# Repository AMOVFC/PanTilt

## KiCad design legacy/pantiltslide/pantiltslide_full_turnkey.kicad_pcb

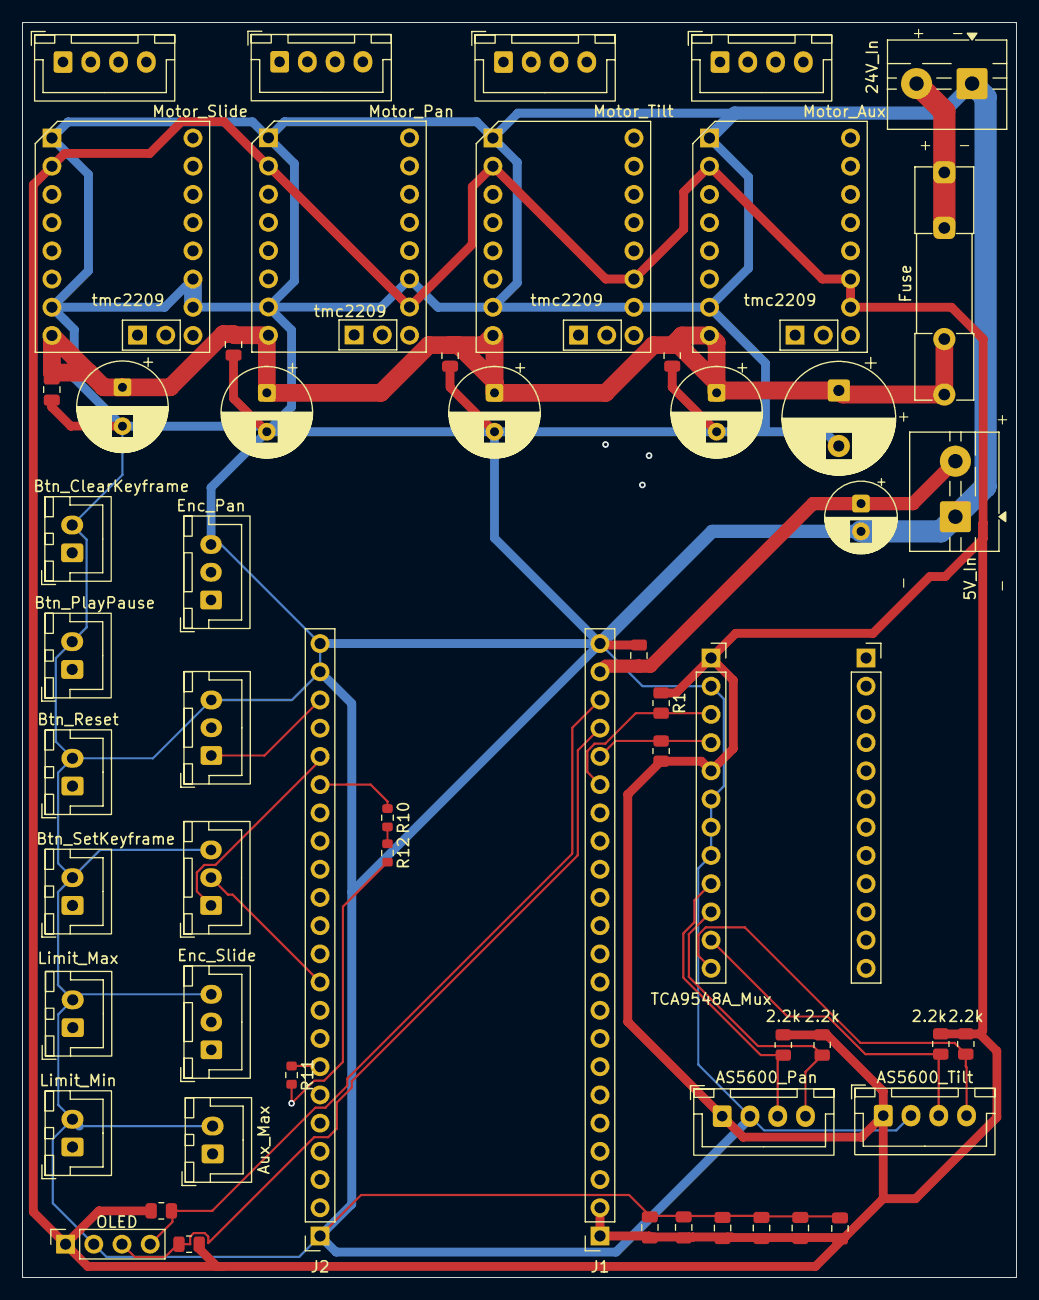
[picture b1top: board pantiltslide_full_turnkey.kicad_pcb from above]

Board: 4 copper layers, 89.5 x 113.0 mm, 57 parts (0 on the bottom side), 57 nets.

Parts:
C1: 470uF/50V; CP_Radial_D10.0mm_P5.00mm
C2, C3, C4, C5: 100uF/50V; CP_Radial_D8.0mm_P3.50mm
C6, C7, C8, C9: 100nF/50V; C_0805_2012Metric
C10: 100uF/16V; CP_Radial_D6.3mm_P2.50mm
C11, C13, C14, C15, C16, C17: 100nF; C_0805_2012Metric
C12: 22uF; C_0805_2012Metric
F1: Fuse; Fuseholder_Clip-5x20mm_Littelfuse_111_Inline_P20.00x5.00mm_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
J1, J2: Conn_01x22_Socket; PinSocket_1x22_P2.54mm_Vertical
J17: Motor_Slide; JST_XH_B4B-XH-A_1x04_P2.50mm_Vertical
J18: Motor_Pan; JST_XH_B4B-XH-A_1x04_P2.50mm_Vertical
J19: Motor_Tilt; JST_XH_B4B-XH-A_1x04_P2.50mm_Vertical
J20, J24: TCA9548A_Mux; PinSocket_1x12_P2.54mm_Vertical
J21: AS5600_Pan; JST_XH_B4B-XH-A_1x04_P2.50mm_Vertical
J22: AS5600_Tilt; JST_XH_B4B-XH-A_1x04_P2.50mm_Vertical
J23: OLED; PinSocket_1x04_P2.54mm_Vertical
J26: Limit_Min; JST_XH_B2B-XH-A_1x02_P2.50mm_Vertical
J27: Limit_Max; JST_XH_B2B-XH-A_1x02_P2.50mm_Vertical
J28: Motor_Aux; JST_XH_B4B-XH-A_1x04_P2.50mm_Vertical
J29: Enc_Slide; JST_XH_B3B-XH-A_1x03_P2.50mm_Vertical
J30: Enc_Pan; JST_XH_B3B-XH-A_1x03_P2.50mm_Vertical
J31: Enc_Tilt; JST_XH_B3B-XH-A_1x03_P2.50mm_Vertical
J32: Enc_Aux; JST_XH_B3B-XH-A_1x03_P2.50mm_Vertical
J33: Btn_SetKeyframe; JST_XH_B2B-XH-A_1x02_P2.50mm_Vertical
J34: Btn_ClearKeyframe; JST_XH_B2B-XH-A_1x02_P2.50mm_Vertical
J35: Btn_PlayPause; JST_XH_B2B-XH-A_1x02_P2.50mm_Vertical
J36: Btn_Reset; JST_XH_B2B-XH-A_1x02_P2.50mm_Vertical
J37: 5V_In; TerminalBlock_MaiXu_MX126-5.0-02P_1x02_P5.00mm
J38: 24V_In; TerminalBlock_MaiXu_MX126-5.0-02P_1x02_P5.00mm
J41: Aux_Max; JST_XH_B2B-XH-A_1x02_P2.50mm_Vertical
R1, R2, R3, R4: 4.7k; R_0805_2012Metric
R5, R6, R7, R8: 2.2k; R_0805_2012Metric
R10, R11: 100R; R_0603_1608Metric
R12: 1k R; R_0603_1608Metric
U1, U2, U3, U4: tmc2209; TMC2209_SilentStepStick_Socket_18P

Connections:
3.3v: C12.1, C13.1, C14.1, C15.1, C16.1, C17.1, J1.1, J1.2, J20.1, J20.5, J21.1, J22.1, J23.1, R1.1, R2.1, R3.1, R4.1, R5.1, R6.1, R7.1, R8.1, U1.2 (VIO), U2.2 (VIO), U2.15 (MS1), U3.2 (VIO), U3.14 (MS2), U4.2 (VIO), U4.14 (MS2), U4.15 (MS1)
+24V: C1.1, C2.1, C3.1, C4.1, C5.1, C6.1, C7.1, C8.1, C9.1, F1.2, U1.8 (VM), U2.8 (VM), U3.8 (VM), U4.8 (VM)
AUX_M1A: J28.1, U4.4 (M1A)
AUX_M1B: J28.2, U4.3 (M1B)
AUX_M2A: J28.3, U4.5 (M2A)
AUX_M2B: J28.4, U4.6 (M2B)
GND: C1.2, C2.2, C3.2, C4.2, C5.2, C6.2, C7.2, C8.2, C9.2, C10.2, C11.2, C12.2, C13.2, C14.2, C15.2, C16.2, C17.2, J1.22, J2.1, J2.21, J2.22, J20.2, J20.6, J20.7, J20.8, J21.2, J22.2, J23.2, J26.2, J27.2, J29.3, J30.3, J31.3, J32.3, J33.2, J34.2, J35.2, J36.2, J37.1, J38.1, J41.2, U1.1 (GND), U1.7 (GND), U1.14 (MS2), U1.15 (MS1), U2.1 (GND), U2.7 (GND), U2.14 (MS2), U3.1 (GND), U3.7 (GND), U3.15 (MS1), U4.1 (GND), U4.7 (GND)
GPIO_1: J2.4, U4.10 (Step)
GPIO_2: J2.5, U4.9 (DIR)
GPIO_3: J1.13, J34.1
GPIO_4: J1.4, U1.10 (Step)
GPIO_5: J1.5, U1.9 (DIR)
GPIO_6: J1.6, U2.10 (Step)
GPIO_7: J1.7, U2.9 (DIR)
GPIO_8: J1.12, U3.10 (Step)
GPIO_9: J1.15, U3.9 (DIR)
GPIO_10: J1.16, U1.16 (En), U2.16 (En), U3.16 (En), U4.16 (En)
GPIO_11: J1.17, J20.3, R1.2
GPIO_12: J1.18, J20.4, R2.2
GPIO_13: J1.19, J23.3, R3.2
GPIO_14: J1.20, J23.4, R4.2
GPIO_15: J1.8, J29.1
GPIO_16: J1.9, J29.2
GPIO_17: J1.10, J30.1
GPIO_18: J1.11, J30.2
GPIO_19: J2.20, J32.1
GPIO_20: J2.19, J32.2
GPIO_21: J2.18, J31.1
GPIO_38: J2.10, J31.2
GPIO_39: J2.9, J26.1
GPIO_40: J2.8, J27.1
GPIO_41: J2.7, R11.1
GPIO_42: J2.6, J41.1
GPIO_45: J2.15, J35.1
GPIO_46: J1.14, J36.1
GPIO_47: J2.17, R10.1
GPIO_48: J2.16, J33.1
MUX_CH0_SCL: J20.10, J21.4, R6.2
MUX_CH0_SDA: J20.9, J21.3, R5.2
MUX_CH1_SCL: J20.12, J22.4, R8.2
MUX_CH1_SDA: J20.11, J22.3, R7.2
unnamed: F1.1, J38.2
unnamed: R10.2, R12.1
PAN_M1A: J18.1, U2.4 (M1A)
PAN_M1B: J18.2, U2.3 (M1B)
PAN_M2A: J18.3, U2.5 (M2A)
PAN_M2B: J18.4, U2.6 (M2B)
SLIDE_M1A: J17.1, U1.4 (M1A)
SLIDE_M1B: J17.2, U1.3 (M1B)
SLIDE_M2A: J17.3, U1.5 (M2A)
SLIDE_M2B: J17.4, U1.6 (M2B)
TILT_M1A: J19.1, U3.4 (M1A)
TILT_M1B: J19.2, U3.3 (M1B)
TILT_M2A: J19.3, U3.5 (M2A)
TILT_M2B: J19.4, U3.6 (M2B)
UART: R11.2, R12.2, U1.11 (PDN), U2.11 (PDN), U3.11 (PDN), U4.11 (PDN)
VCC_5V: C10.1, C11.1, J1.21, J37.2

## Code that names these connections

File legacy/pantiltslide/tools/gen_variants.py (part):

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# where rise time actually gets tight - hence the stronger value there.

PULLUP_NETS = [
    ("GPIO_11", "4.7k"),           # bus A SDA
    ("GPIO_12", "4.7k"),           # bus A SCL
    ("GPIO_13", "4.7k"),           # bus B SDA
    ("GPIO_14", "4.7k"),           # bus B SCL
    ("MUX_CH0_SDA", "2.2k"),
    ("MUX_CH0_SCL", "2.2k"),
    ("MUX_CH1_SDA", "2.2k"),
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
